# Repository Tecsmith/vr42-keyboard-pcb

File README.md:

# VR42 Keyboard PCB

<blockquote align="center"><b>NB:</b> This project design is complete, but has not been prototyped for validation.</blockquote>

## Intent

A 42-key micro keyboard designed for QMK with specific focus on ultra fast key scan rates / poll rates to make for an ideal gaming keyboard.

#### Progression

- See [CHANGELOG.md](CHANGELOG.md)

## Case

This case is designed in conjunction with the [VR42 Keyboard Case](https://github.com/tecsmith/vr42-keyboard-case).  These two projects are mutually inclusive and built as one solution.

## Resources

### Schematic
 - PDF [here](docs/vr42-revB.pdf)

### MCU PCB
 - EAGLE BRD *(PCB)* [here](EAGLE/vr42/vr42-revB-kbd.brd)
 - EAGLE SCH *(Schematic)* [here](EAGLE/vr42/vr42-revB-kbd.sch)

### Key Switch PCB
 - EAGLE BRD *(PCB)* [here](EAGLE/vr42/vr42-revB-kbd.brd)
 - EAGLE SCH *(Schematic)* [here](EAGLE/vr42/vr42-revB-kbd.sch)

### Beta PCB renders

#### Top

#### Bottom *(Component side)*

#### Intra-Board Connectors

You will need 3x Molex Pico-EZMate cables

|                                                                 | Cable | Usage                                |
|:---------------------------------------------------------------:|:-----:|:-------------------------------------|
| </img> | 6 way | Keyboard Matrix SPI interface        |
| </img> | 4 way | USB connection to UBD                |
| </img> | 3 way | ARGB to drive status & per-key LED's |

### Layout ideation renders

#### Render

#### Layout

#### Matrix coordinates *(QMK & VIA)*

## Planned Features

- [ ] QMK / VIA build
- [ ] 1x `STM32F405` STM32 CPU *(ft. dual USB, one is FS, the other HS)*
- [ ] 1x `TS3USB221` USB 2.0 Multiplexer for USB port selection *(based on [akeypad](https://github.com/luantty2/akeypad) )*
- [ ] 1x `USB3300-EZK` Hi-Speed USB Host for OTG PHY pin interface
- [ ] ~~1x `W25Q64JW` 8K SPI Flash Module~~ *[Not needed, the MCU has 512K Flash]*
- [ ] 1x `M95640-DRE` 8K SPI EEPROM Module
- [ ] 6x `MC74HC589A` SPI Input Shift Registers
    - No QMK key matrix, using all direct pins for faster scan rates
    - Scan via individually grounded keys on shift registers
- [ ] 2x `IS31FL3746B` SPI LED Matrix Drivers
    - 43x RGB LED's
    - With power on/off `TPS22995H-Q1` load switchs, 1 per
- [ ] C4 *(or S1)* UDB USB-C by @ai03 - see [here](https://github.com/ai03-2725/Unified-Daughterboard)

## Possible BIG issues

- [x] ~~With very limited PCB space, 13x IC's may not fit :(~~ *[Resolved with separate key and MCU PCB's]*
- [ ] ~~Not sure QMK can handle High Speed USB~~ *[It can, just now need to do it :( )]*
- [ ] Not sure dual USB is switchable with the USB multiplexer *[Needs to be coded for and tested]*
    - FS USB required for Bootloader
    - HS USB required for >1KHz polling rates

&nbsp;<br>&nbsp;
---
Made with &#9829; by **Vino Rodrigues**

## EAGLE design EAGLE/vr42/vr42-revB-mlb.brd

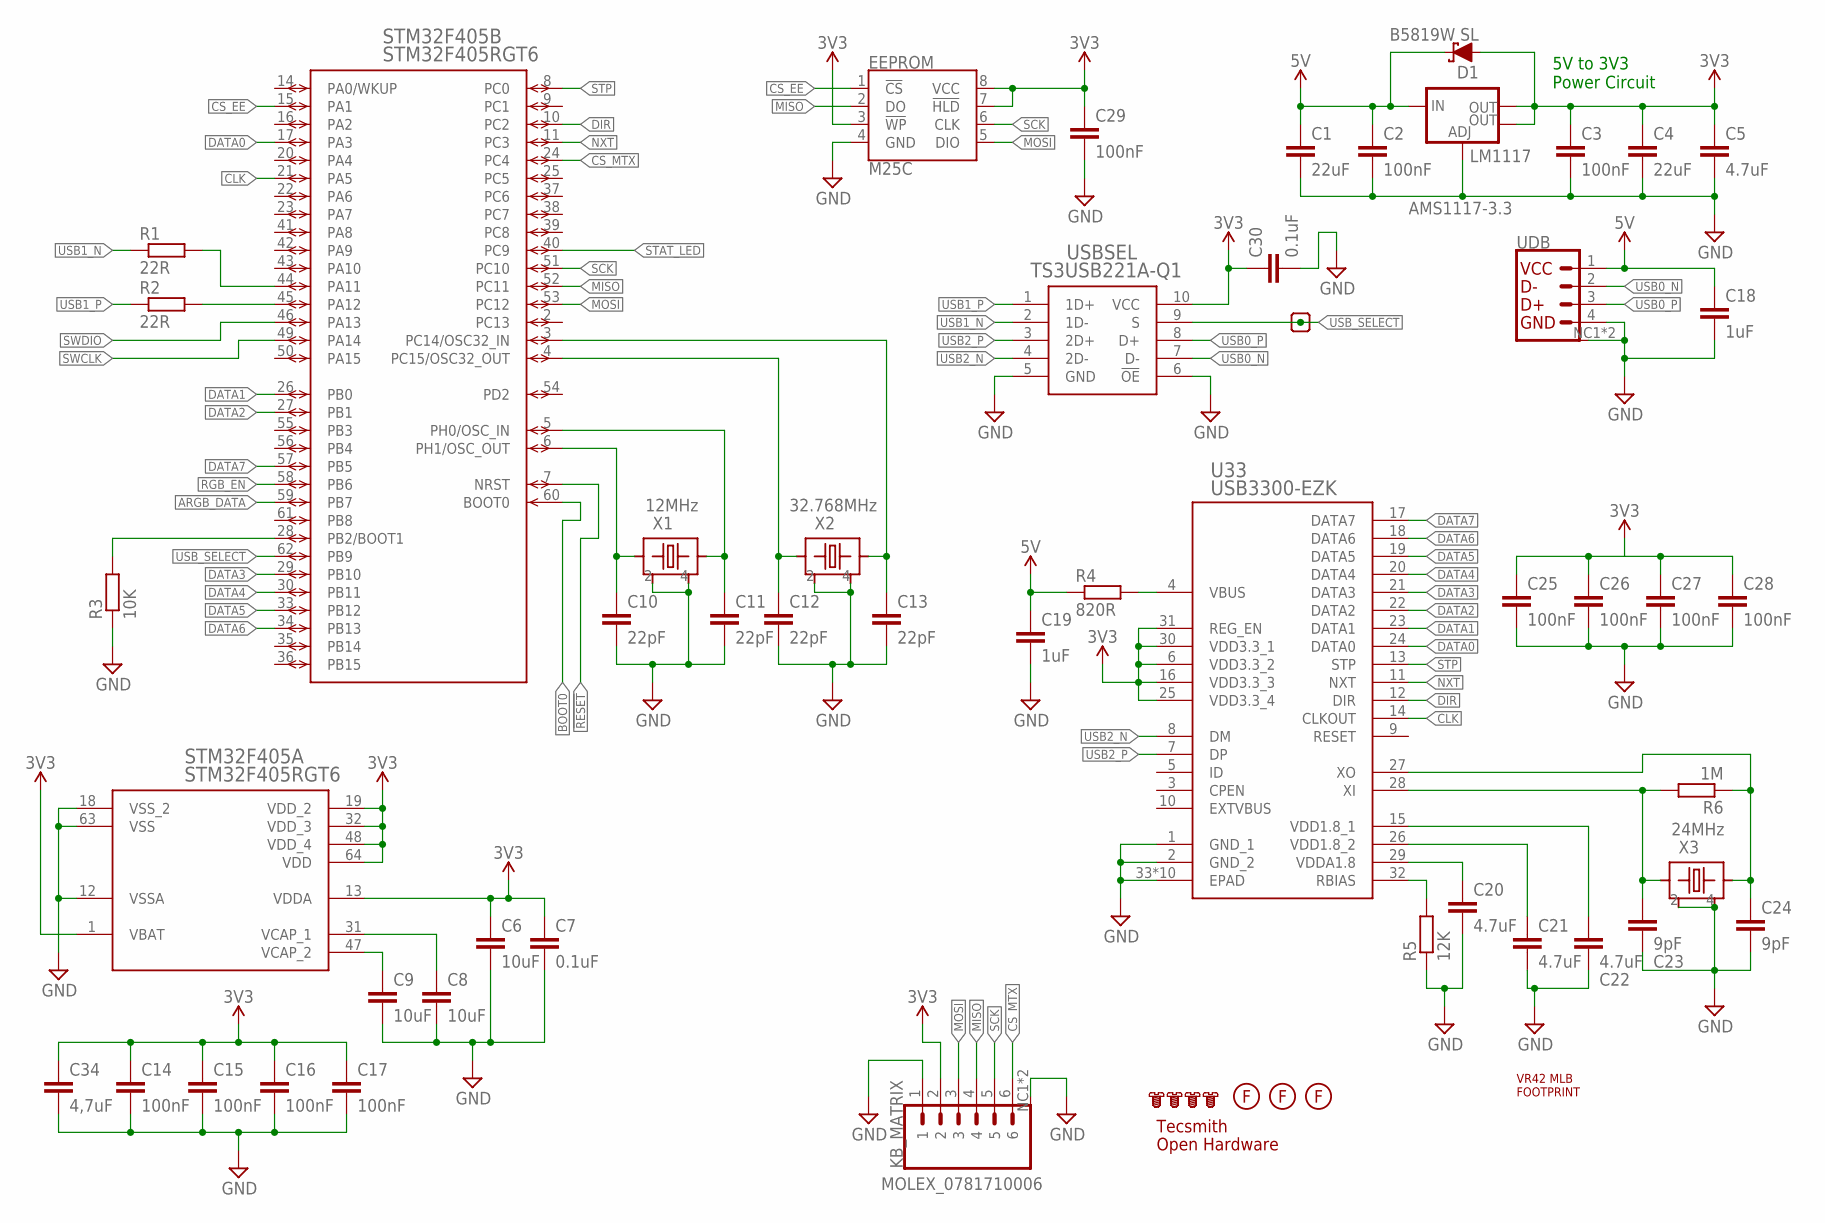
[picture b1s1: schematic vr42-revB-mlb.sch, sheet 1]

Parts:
C1, C4: 22uF; C0603
C2, C3, C14, C15, C16, C17, C25, C26, C27, C28, C29: 100nF; C0603
C5, C20, C21, C22: 4.7uF; C0603
C6, C8, C9: 10uF; C0603
C7, C30: 0.1uF; C0603
C10, C11, C12, C13: 22pF; C0603
C18, C19: 1uF; C0603
C23, C24: 9pF; C0603
C34: 4,7uF; C0603
D1: B5819W SL; SOD-123
EEPROM: M25C; 8-SOIC
KB_MATRIX: MOLEX_0781710006; MOLEX_781710006
LM1117: AMS1117-3.3; SOT223
LOGO1: OSHW-LOGOM; OSHW-LOGO-M
R1, R2: 22R; R0603
R3: 10K; R0603
R4: 820R; R0603
R5: 12K; R0603
R6: 1M; R0603
STM32F405: STM32F405RGT6; LQFP64-10X10MM
TP1: TEST-POINT.3RN; PAD.03X.03-RN
U33: USB3300-EZK; QFN32_5X5MC_MCH
U$1: VR42_MLB_FOOTPRINT
U$2, U$3, U$4, U$5: MOUNTING-HOLE
U$6: TECSMITH-LOGOLONG; TECSMITH-NAME
U$7, U$8, U$9: FIDUCIAL
UDB: UBD-S1_C4; MOLEX_781710004
USBSEL: TS3USB221A-Q1; RSE10
X1: 12MHz; CRYSTAL_2.5X2
X2: 32.768MHz; CRYSTAL_2.5X2
X3: 24MHz; CRYSTAL_2.5X2

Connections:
!RESET: STM32F405.7 (NRST); also elsewhere on the board
ARGB_DATA: STM32F405.59 (PB7); also elsewhere on the board
BOOT0: STM32F405.60 (BOOT0); also elsewhere on the board
BOOT1: R3.2, STM32F405.28 (PB2/BOOT1)
CLK: STM32F405.21 (PA5), U33.14 (CLKOUT)
CS_EE: EEPROM.1 (!CS), STM32F405.15 (PA1)
CS_MTX: KB_MATRIX.6, STM32F405.24 (PC4)
DATA0: STM32F405.17 (PA3), U33.24 (DATA0)
DATA1: STM32F405.26 (PB0), U33.23 (DATA1)
DATA2: STM32F405.27 (PB1), U33.22 (DATA2)
DATA3: STM32F405.29 (PB10), U33.21 (DATA3)
DATA4: STM32F405.30 (PB11), U33.20 (DATA4)
DATA5: STM32F405.33 (PB12), U33.19 (DATA5)
DATA6: STM32F405.34 (PB13), U33.18 (DATA6)
DATA7: STM32F405.57 (PB5), U33.17 (DATA7)
DIR: STM32F405.10 (PC2), U33.12 (DIR)
GND: C1.2, C2.2, C3.2, C4.2, C5.2, C6.2, C7.2, C8.2, C9.2, C10.2, C11.2, C12.2, C13.2, C14.2, C15.2, C16.2, C17.2, C18.2, C19.2, C20.2, C21.2, C22.2, C23.2, C24.2, C25.2, C26.2, C27.2, C28.2, C29.2, C30.2, C34.2, EEPROM.4 (GND), KB_MATRIX.1, KB_MATRIX.NC1 (M), KB_MATRIX.NC2 (M), LM1117.1 (ADJ), R3.1, R5.1, STM32F405.12 (VSSA), STM32F405.18 (VSS_2), STM32F405.63 (VSS), U33.1 (GND_1), U33.2 (GND_2), U33.33 (EPAD), U33.P$1 (EPAD), U33.P$2 (EPAD), U33.P$3 (EPAD), U33.P$4 (EPAD), U33.P$5 (EPAD), U33.P$6 (EPAD), U33.P$7 (EPAD), U33.P$8 (EPAD), U33.P$9 (EPAD), UDB.4 (GND), UDB.NC1 (M), UDB.NC2 (M), USBSEL.5 (GND), USBSEL.6 (!OE), X1.2, X1.4, X2.2, X2.4, X3.2, X3.4; also elsewhere on the board
MISO: EEPROM.2 (DO), KB_MATRIX.4, STM32F405.52 (PC11)
MOSI: EEPROM.5 (DIO), KB_MATRIX.3, STM32F405.53 (PC12)
unnamed: R1.2, STM32F405.44 (PA11)
unnamed: R2.2, STM32F405.45 (PA12)
unnamed: R4.2, U33.4 (VBUS)
unnamed: C20.1, U33.29 (VDDA1.8)
unnamed: C21.1, U33.26 (VDD1.8_2)
unnamed: C22.1, U33.15 (VDD1.8_1)
unnamed: C23.1, R6.2, U33.28 (XI), X3.1
unnamed: C24.1, R6.1, U33.27 (XO), X3.3
NXT: STM32F405.11 (PC3), U33.11 (NXT)
OSC32_IN: C13.1, STM32F405.3 (PC14/OSC32_IN), X2.3
OSC32_OUT: C12.1, STM32F405.4 (PC15/OSC32_OUT), X2.1
OSC_IN: C11.1, STM32F405.5 (PH0/OSC_IN), X1.3
OSC_OUT: C10.1, STM32F405.6 (PH1/OSC_OUT), X1.1
P$1: U$2.P$1, U$2.P$2, U$2.P$3, U$2.P$4, U$2.P$5, U$2.P$6, U$3.P$1, U$3.P$2, U$3.P$3, U$3.P$4, U$3.P$5, U$3.P$6, U$4.P$1, U$4.P$2, U$4.P$3, U$4.P$4, U$4.P$5, U$4.P$6, U$5.P$1, U$5.P$2, U$5.P$3, U$5.P$4, U$5.P$5, U$5.P$6
RBIAS: R5.2, U33.32 (RBIAS)
RGB_EN: STM32F405.58 (PB6); also elsewhere on the board
SCK: EEPROM.6 (CLK), KB_MATRIX.5, STM32F405.51 (PC10)
STAT_LED: STM32F405.40 (PC9); also elsewhere on the board
STP: STM32F405.8 (PC0), U33.13 (STP)
SWCLK: STM32F405.49 (PA14); also elsewhere on the board
SWDIO: STM32F405.46 (PA13); also elsewhere on the board
USB0_N: UDB.2 (DN), USBSEL.7 (D-)
USB0_P: UDB.3 (DP), USBSEL.8 (D+)
USB1_N: R1.1, USBSEL.2 (1D-)
USB1_P: R2.1, USBSEL.1 (1D+)
USB2_N: U33.8 (DM), USBSEL.4 (2D-)
USB2_P: U33.7 (DP), USBSEL.3 (2D+)
USB_SELECT: STM32F405.62 (PB9), TP1.1, USBSEL.9 (S)
VCAP1: C8.1, STM32F405.31 (VCAP_1)
VCAP2: C9.1, STM32F405.47 (VCAP_2)
VCC_1: C1.1, C2.1, C18.1, C19.1, D1.C, LM1117.3 (IN), R4.1, UDB.1 (VCC); also elsewhere on the board
VCC_2: C3.1, C4.1, C5.1, C6.1, C7.1, C14.1, C15.1, C16.1, C17.1, C25.1, C26.1, C27.1, C28.1, C29.1, C30.1, C34.1, D1.A, EEPROM.3 (!WP), EEPROM.7 (!HLD), EEPROM.8 (VCC), KB_MATRIX.2, LM1117.2 (OUT), LM1117.4 (OUT), STM32F405.1 (VBAT), STM32F405.13 (VDDA), STM32F405.19 (VDD_2), STM32F405.32 (VDD_3), STM32F405.48 (VDD_4), STM32F405.64 (VDD), U33.6 (VDD3.3_2), U33.16 (VDD3.3_3), U33.25 (VDD3.3_4), U33.30 (VDD3.3_1), U33.31 (REG_EN), USBSEL.10 (VCC); also elsewhere on the board

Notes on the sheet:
5V to 3V3 Power Circuit

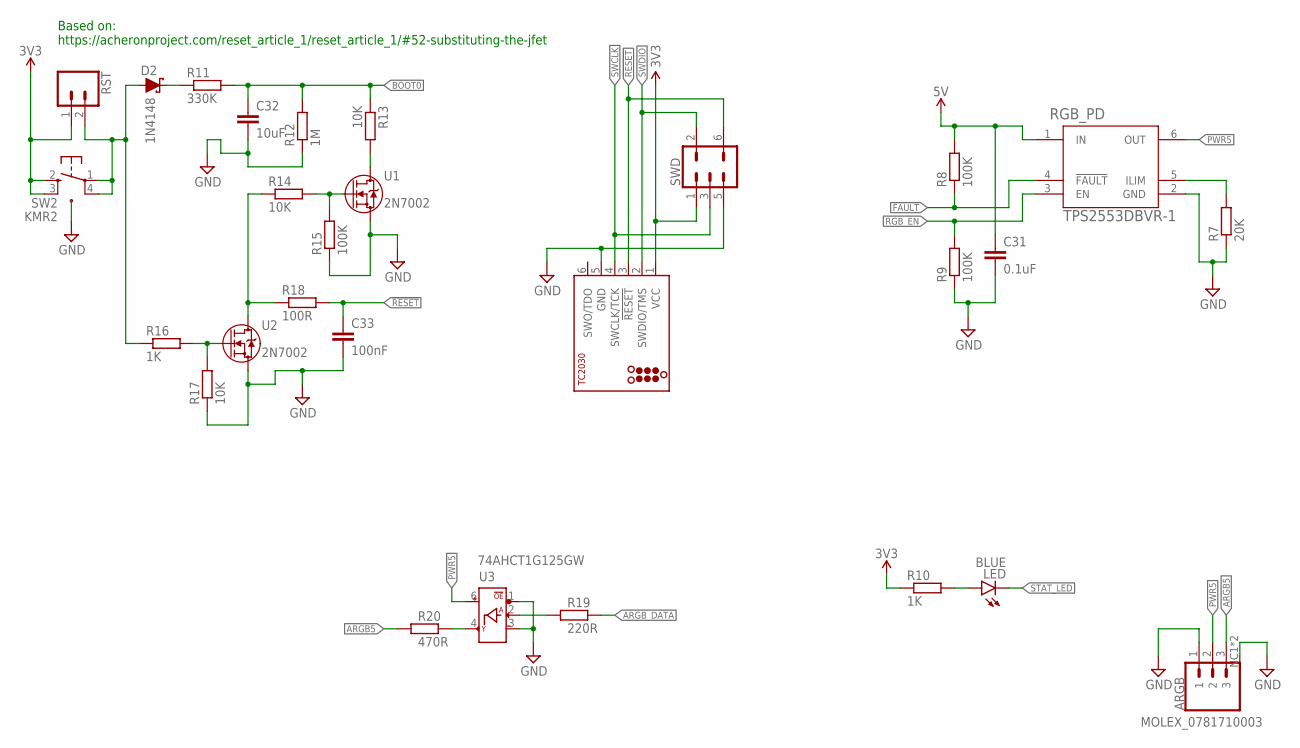
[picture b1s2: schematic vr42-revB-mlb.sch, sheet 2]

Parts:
ARGB: MOLEX_0781710003; MOLEX_781710003
C31: 0.1uF; C0603
C32: 10uF; C0603
C33: 100nF; C0603
D2: 1N4148; SOD-123
LED: BLUE; SML0603
R7: 20K; R0603
R8, R9, R15: 100K; R0603
R10, R16: 1K; R0603
R11: 330K; R0603
R12: 1M; R0603
R13, R14, R17: 10K; R0603
R18: 100R; R0603
R19: 220R; R0603
R20: 470R; R0603
RGB_PD: TPS2553DBVR-1; DBV0006A_N
RST: CONN_02; 1X02
SW2: KMR2; SW4_KMR221GLFS_CNK
SWD: SWD-5PIN; PAD_05_03X2_TP_NO4
TC: TC2030-MCP-NL
U1, U2: 2N7002; TO-236AB_NEX
U3: 74AHCT1G125GW; SC-88A__TSSOP5__SOT353-1

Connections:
!FAULT: R8.1, RGB_PD.4 (!FAULT)
!RESET: C33.1, R18.2, SWD.6, TC.3 (!RESET); also elsewhere on the board
ARGB5: ARGB.3, R20.1
ARGB_DATA: R19.2; also elsewhere on the board
BOOT0: C32.1, R11.2, R12.2, R13.1; also elsewhere on the board
GND: ARGB.1, ARGB.NC1 (M), ARGB.NC2 (M), C31.2, C32.2, C33.2, R7.1, R9.1, R12.1, R15.1, R17.1, RGB_PD.2 (GND), SW2.5, SWD.5, TC.5 (GND), U1.2 (3), U2.2 (3), U3.1 (!OE), U3.3 (3_GND); also elsewhere on the board
unnamed: D2.C, R11.1
unnamed: LED.A, R10.2
unnamed: R7.2, RGB_PD.5 (ILIM)
unnamed: R14.1, R18.1, U2.3 (2)
unnamed: R13.2, U1.3 (2)
unnamed: R14.2, R15.2, U1.1
unnamed: R19.1, U3.2 (A_DIN)
unnamed: R16.2, R17.2, U2.1
unnamed: D2.A, R16.1, RST.2, SW2.1, SW2.4
unnamed: R20.2, U3.4 (Y_DOUT)
PWR5: ARGB.2, RGB_PD.6 (OUT), U3.6 (5_VCC)
RGB_EN: R9.2, RGB_PD.3 (EN); also elsewhere on the board
STAT_LED: LED.C; also elsewhere on the board
SWCLK: SWD.3, TC.4 (SWCLK/TCK); also elsewhere on the board
SWDIO: SWD.2, TC.2 (SWDIO/TMS); also elsewhere on the board
VCC_1: C31.1, R8.2, RGB_PD.1 (IN); also elsewhere on the board
VCC_2: R10.1, RST.1, SW2.2, SW2.3, SWD.1, TC.1 (VCC); also elsewhere on the board

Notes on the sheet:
Based on: https://acheronproject.com/reset_article_1/reset_article_1/#52-substituting-the-jfet

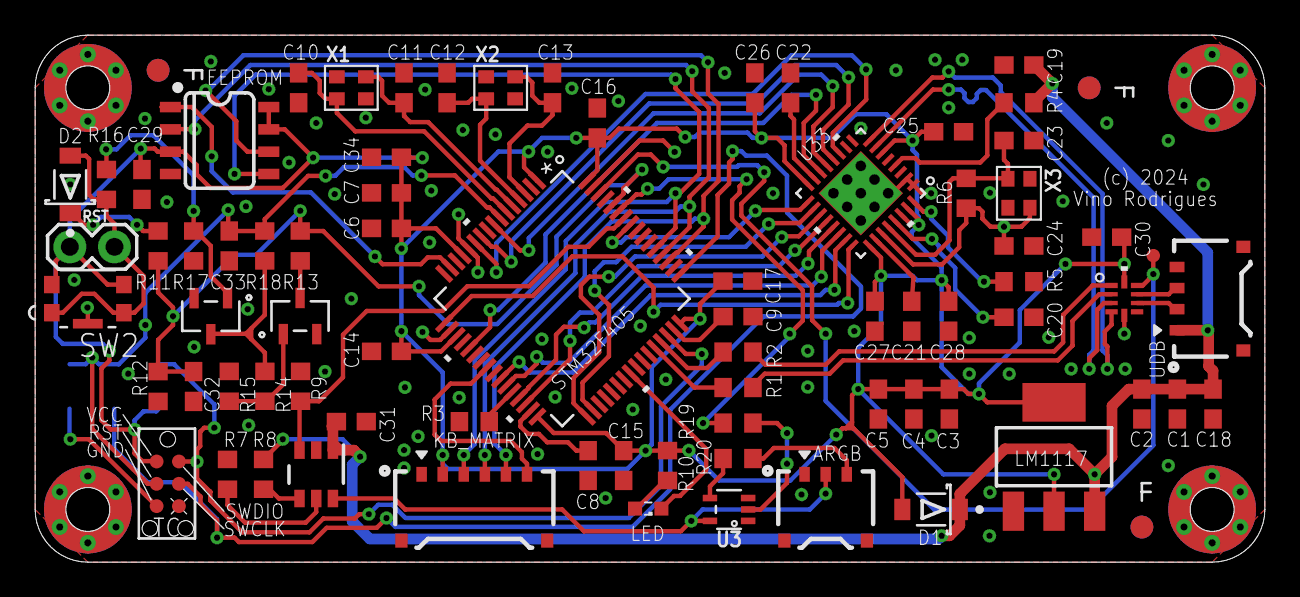
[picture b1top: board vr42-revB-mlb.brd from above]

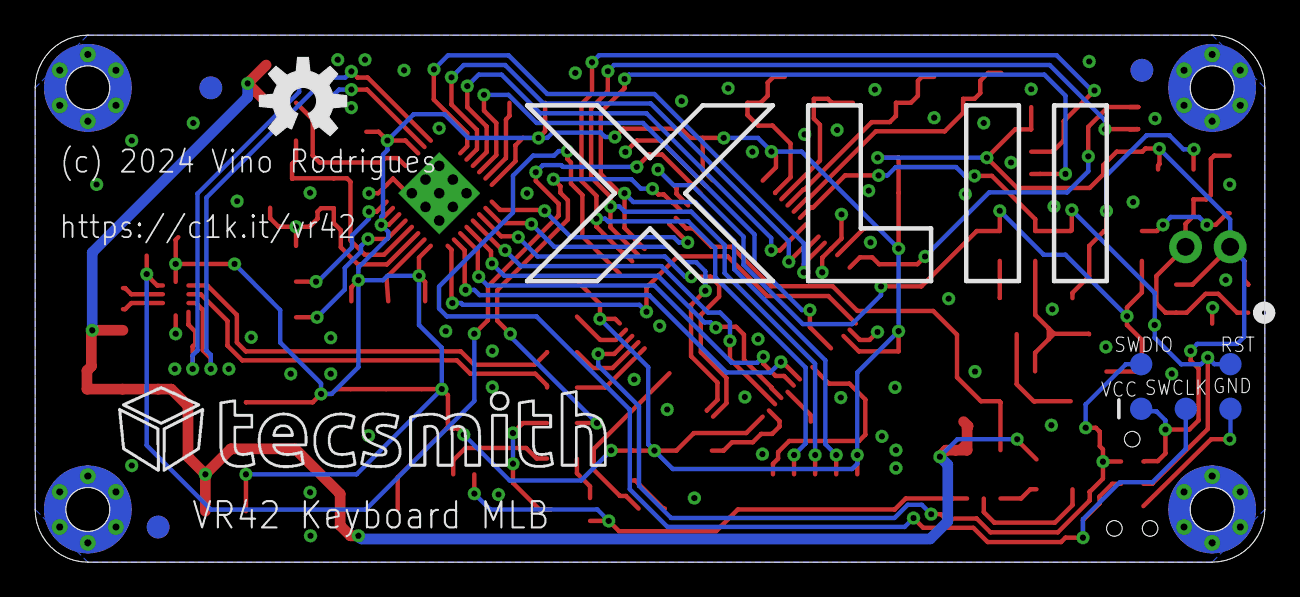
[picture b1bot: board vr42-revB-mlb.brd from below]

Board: 4 copper layers, 70.0 x 30.0 mm, 87 parts (3 on the bottom side), 64 nets.

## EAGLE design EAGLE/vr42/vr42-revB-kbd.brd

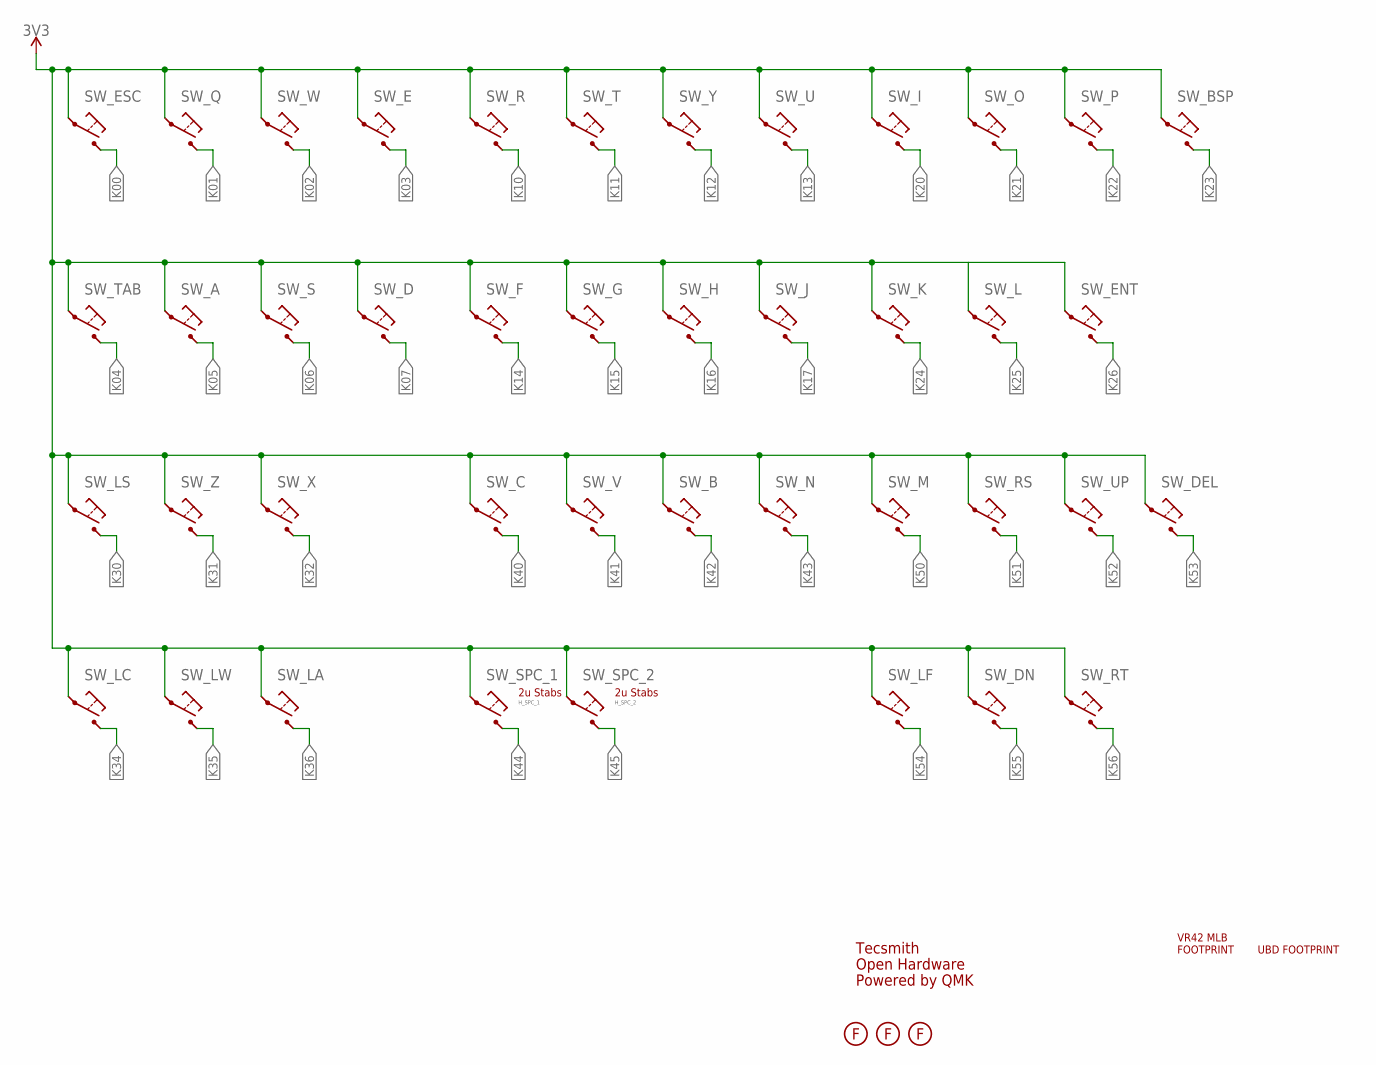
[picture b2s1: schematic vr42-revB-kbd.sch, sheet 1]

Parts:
H_SPC_1, H_SPC_2: MX-STABS-200U
LOGO1: OSHW-LOGOL; OSHW-LOGO-L
SW_A: MX-5-PIN-HOTSWAP-PAD
SW_B: MX-5-PIN-HOTSWAP-PAD
SW_BSP: MX-5-PIN-HOTSWAP-PAD
SW_C: MX-5-PIN-HOTSWAP-PAD
SW_D: MX-5-PIN-HOTSWAP-PAD
SW_DEL: MX-5-PIN-HOTSWAP-PAD
SW_DN: MX-5-PIN-HOTSWAP-PAD
SW_E: MX-5-PIN-HOTSWAP-PAD
SW_ENT: MX-5-PIN-HOTSWAP-PAD
SW_ESC: MX-5-PIN-HOTSWAP-PAD
SW_F: MX-5-PIN-HOTSWAP-PAD
SW_G: MX-5-PIN-HOTSWAP-PAD
SW_H: MX-5-PIN-HOTSWAP-PAD
SW_I: MX-5-PIN-HOTSWAP-PAD
SW_J: MX-5-PIN-HOTSWAP-PAD
SW_K: MX-5-PIN-HOTSWAP-PAD
SW_L: MX-5-PIN-HOTSWAP-PAD
SW_LA: MX-5-PIN-HOTSWAP-PAD
SW_LC: MX-5-PIN-HOTSWAP-PAD
SW_LF: MX-5-PIN-HOTSWAP-PAD
SW_LS: MX-5-PIN-HOTSWAP-PAD
SW_LW: MX-5-PIN-HOTSWAP-PAD
SW_M: MX-5-PIN-HOTSWAP-PAD
SW_N: MX-5-PIN-HOTSWAP-PAD
SW_O: MX-5-PIN-HOTSWAP-PAD
SW_P: MX-5-PIN-HOTSWAP-PAD
SW_Q: MX-5-PIN-HOTSWAP-PAD
SW_R: MX-5-PIN-HOTSWAP-PAD
SW_RS: MX-5-PIN-HOTSWAP-PAD
SW_RT: MX-5-PIN-HOTSWAP-PAD
SW_S: MX-5-PIN-HOTSWAP-PAD
SW_SPC_1, SW_SPC_2: MX-5-PIN-HOTSWAP-PAD
SW_T: MX-5-PIN-HOTSWAP-PAD
SW_TAB: MX-5-PIN-HOTSWAP-PAD
SW_U: MX-5-PIN-HOTSWAP-PAD
SW_UP: MX-5-PIN-HOTSWAP-PAD
SW_V: MX-5-PIN-HOTSWAP-PAD
SW_W: MX-5-PIN-HOTSWAP-PAD
SW_X: MX-5-PIN-HOTSWAP-PAD
SW_Y: MX-5-PIN-HOTSWAP-PAD
SW_Z: MX-5-PIN-HOTSWAP-PAD
U$1: VR42_MLB_FOOTPRINT
U$2: UBD_FOOTPRINT; UDB_FOOTPRINT
U$3: TECSMITH-LOGOLONG; TECSMITH-NAME
U$4: QMK_LOGO
U$5, U$6, U$7: FIDUCIAL

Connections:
K00: SW_ESC.1@1, SW_ESC.1@2; also elsewhere on the board
K01: SW_Q.1@1, SW_Q.1@2; also elsewhere on the board
K02: SW_W.1@1, SW_W.1@2; also elsewhere on the board
K03: SW_E.1@1, SW_E.1@2; also elsewhere on the board
K04: SW_TAB.1@1, SW_TAB.1@2; also elsewhere on the board
K05: SW_A.1@1, SW_A.1@2; also elsewhere on the board
K06: SW_S.1@1, SW_S.1@2; also elsewhere on the board
K07: SW_D.1@1, SW_D.1@2; also elsewhere on the board
K10: SW_R.1@1, SW_R.1@2; also elsewhere on the board
K11: SW_T.1@1, SW_T.1@2; also elsewhere on the board
K12: SW_Y.1@1, SW_Y.1@2; also elsewhere on the board
K13: SW_U.1@1, SW_U.1@2; also elsewhere on the board
K14: SW_F.1@1, SW_F.1@2; also elsewhere on the board
K15: SW_G.1@1, SW_G.1@2; also elsewhere on the board
K16: SW_H.1@1, SW_H.1@2; also elsewhere on the board
K17: SW_J.1@1, SW_J.1@2; also elsewhere on the board
K20: SW_I.1@1, SW_I.1@2; also elsewhere on the board
K21: SW_O.1@1, SW_O.1@2; also elsewhere on the board
K22: SW_P.1@1, SW_P.1@2; also elsewhere on the board
K23: SW_BSP.1@1, SW_BSP.1@2; also elsewhere on the board
K24: SW_K.1@1, SW_K.1@2; also elsewhere on the board
K25: SW_L.1@1, SW_L.1@2; also elsewhere on the board
K26: SW_ENT.1@1, SW_ENT.1@2; also elsewhere on the board
K30: SW_LS.1@1, SW_LS.1@2; also elsewhere on the board
K31: SW_Z.1@1, SW_Z.1@2; also elsewhere on the board
K32: SW_X.1@1, SW_X.1@2; also elsewhere on the board
K34: SW_LC.1@1, SW_LC.1@2; also elsewhere on the board
K35: SW_LW.1@1, SW_LW.1@2; also elsewhere on the board
K36: SW_LA.1@1, SW_LA.1@2; also elsewhere on the board
K40: SW_C.1@1, SW_C.1@2; also elsewhere on the board
K41: SW_V.1@1, SW_V.1@2; also elsewhere on the board
K42: SW_B.1@1, SW_B.1@2; also elsewhere on the board
K43: SW_N.1@1, SW_N.1@2; also elsewhere on the board
K44: SW_SPC_1.1@1, SW_SPC_1.1@2; also elsewhere on the board
K45: SW_SPC_2.1@1, SW_SPC_2.1@2; also elsewhere on the board
K50: SW_M.1@1, SW_M.1@2; also elsewhere on the board
K51: SW_RS.1@1, SW_RS.1@2; also elsewhere on the board
K52: SW_UP.1@1, SW_UP.1@2; also elsewhere on the board
K53: SW_DEL.1@1, SW_DEL.1@2; also elsewhere on the board
K54: SW_LF.1@1, SW_LF.1@2; also elsewhere on the board
K55: SW_DN.1@1, SW_DN.1@2; also elsewhere on the board
K56: SW_RT.1@1, SW_RT.1@2; also elsewhere on the board
VCC_2: SW_A.2@1 (S), SW_A.2@2 (S), SW_B.2@1 (S), SW_B.2@2 (S), SW_BSP.2@1 (S), SW_BSP.2@2 (S), SW_C.2@1 (S), SW_C.2@2 (S), SW_D.2@1 (S), SW_D.2@2 (S), SW_DEL.2@1 (S), SW_DEL.2@2 (S), SW_DN.2@1 (S), SW_DN.2@2 (S), SW_E.2@1 (S), SW_E.2@2 (S), SW_ENT.2@1 (S), SW_ENT.2@2 (S), SW_ESC.2@1 (S), SW_ESC.2@2 (S), SW_F.2@1 (S), SW_F.2@2 (S), SW_G.2@1 (S), SW_G.2@2 (S), SW_H.2@1 (S), SW_H.2@2 (S), SW_I.2@1 (S), SW_I.2@2 (S), SW_J.2@1 (S), SW_J.2@2 (S), SW_K.2@1 (S), SW_K.2@2 (S), SW_L.2@1 (S), SW_L.2@2 (S), SW_LA.2@1 (S), SW_LA.2@2 (S), SW_LC.2@1 (S), SW_LC.2@2 (S), SW_LF.2@1 (S), SW_LF.2@2 (S), SW_LS.2@1 (S), SW_LS.2@2 (S), SW_LW.2@1 (S), SW_LW.2@2 (S), SW_M.2@1 (S), SW_M.2@2 (S), SW_N.2@1 (S), SW_N.2@2 (S), SW_O.2@1 (S), SW_O.2@2 (S), SW_P.2@1 (S), SW_P.2@2 (S), SW_Q.2@1 (S), SW_Q.2@2 (S), SW_R.2@1 (S), SW_R.2@2 (S), SW_RS.2@1 (S), SW_RS.2@2 (S), SW_RT.2@1 (S), SW_RT.2@2 (S), SW_S.2@1 (S), SW_S.2@2 (S), SW_SPC_1.2@1 (S), SW_SPC_1.2@2 (S), SW_SPC_2.2@1 (S), SW_SPC_2.2@2 (S), SW_T.2@1 (S), SW_T.2@2 (S), SW_TAB.2@1 (S), SW_TAB.2@2 (S), SW_U.2@1 (S), SW_U.2@2 (S), SW_UP.2@1 (S), SW_UP.2@2 (S), SW_V.2@1 (S), SW_V.2@2 (S), SW_W.2@1 (S), SW_W.2@2 (S), SW_X.2@1 (S), SW_X.2@2 (S), SW_Y.2@1 (S), SW_Y.2@2 (S), SW_Z.2@1 (S), SW_Z.2@2 (S); also elsewhere on the board

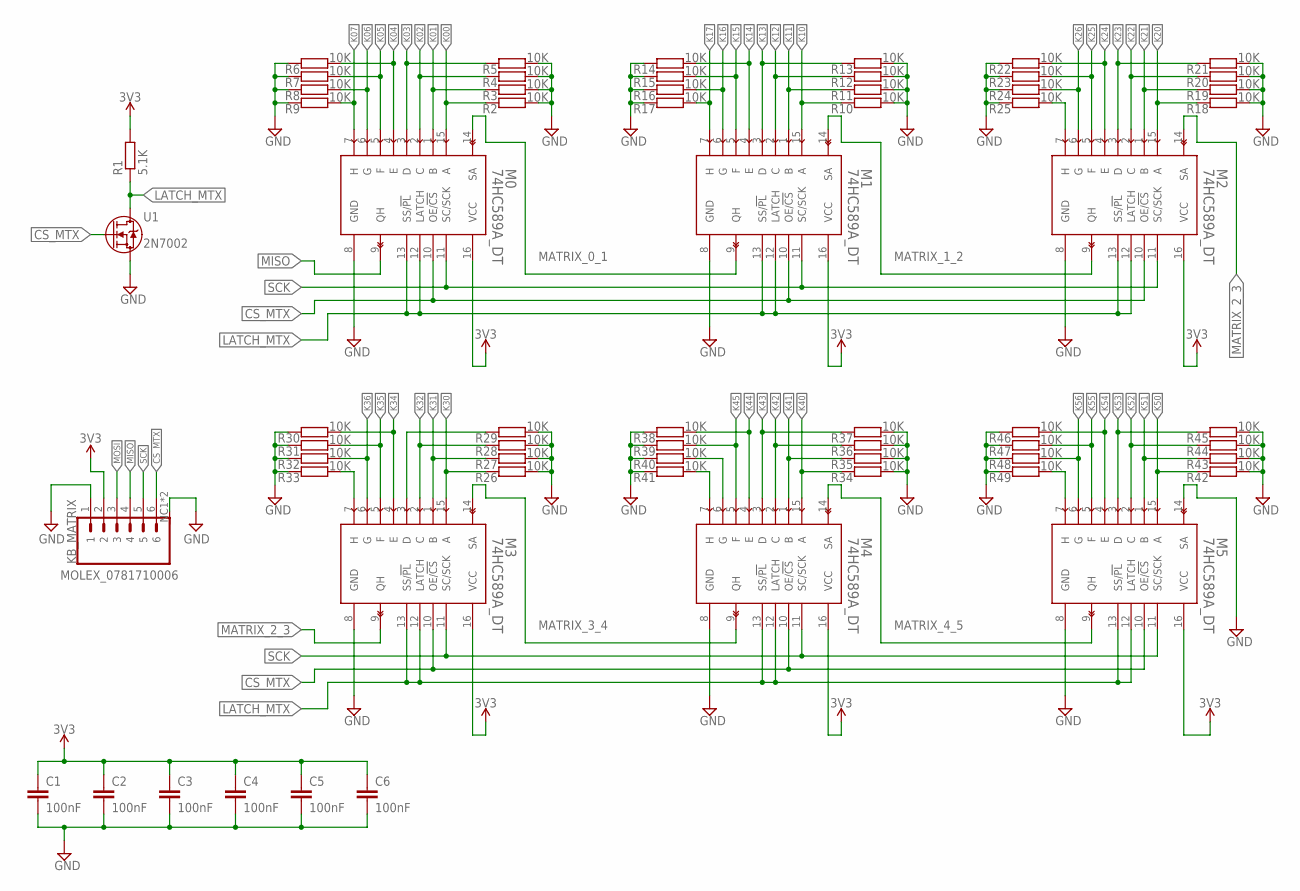
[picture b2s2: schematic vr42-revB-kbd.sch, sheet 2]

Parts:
C1, C2, C3, C4, C5, C6: 100nF; C0603
KB_MATRIX: MOLEX_0781710006; MOLEX_781710006
M0, M1, M2, M3, M4, M5: 74HC589A_DT; TSSOP16
R1: 5.1K; R0603
R2, R3, R4, R5, R6, R7, R8, R9, R10, R11, R12, R13, R14, R15, R16, R17, R18, R19, R20, R21, R22, R23, R24, R25, R26, R27, R28, R29, R30, R31, R32, R33, R34, R35, R36, R37, R38, R39, R40, R41, R42, R43, R44, R45, R46, R47, R48, R49: 10K; R0603
U1: 2N7002; TO-236AB_NEX

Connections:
CS_MTX: KB_MATRIX.6, M0.10 (OE/!CS), M1.10 (OE/!CS), M2.10 (OE/!CS), M3.10 (OE/!CS), M4.10 (OE/!CS), M5.10 (OE/!CS), U1.1
GND: C1.2, C2.2, C3.2, C4.2, C5.2, C6.2, KB_MATRIX.1, KB_MATRIX.NC1 (M), KB_MATRIX.NC2 (M), M0.8 (GND), M1.8 (GND), M2.8 (GND), M3.8 (GND), M4.8 (GND), M5.8 (GND), M5.14 (SA), R2.1, R3.1, R4.1, R5.1, R6.2, R7.2, R8.2, R9.2, R10.1, R11.1, R12.1, R13.1, R14.2, R15.2, R16.2, R17.2, R18.1, R19.1, R20.1, R21.1, R22.2, R23.2, R24.2, R25.2, R26.1, R27.1, R28.1, R29.1, R30.2, R31.2, R32.2, R33.2, R34.1, R35.1, R36.1, R37.1, R38.2, R39.2, R40.2, R41.2, R42.1, R43.1, R44.1, R45.1, R46.2, R47.2, R48.2, R49.2, U1.2 (3); also elsewhere on the board
K00: M0.15 (A), R2.2; also elsewhere on the board
K01: M0.1 (B), R3.2; also elsewhere on the board
K02: M0.2 (C), R4.2; also elsewhere on the board
K03: M0.3 (D), R5.2; also elsewhere on the board
K04: M0.4 (E), R6.1; also elsewhere on the board
K05: M0.5 (F), R7.1; also elsewhere on the board
K06: M0.6 (G), R8.1; also elsewhere on the board
K07: M0.7 (H), R9.1; also elsewhere on the board
K10: M1.15 (A), R10.2; also elsewhere on the board
K11: M1.1 (B), R11.2; also elsewhere on the board
K12: M1.2 (C), R12.2; also elsewhere on the board
K13: M1.3 (D), R13.2; also elsewhere on the board
K14: M1.4 (E), R14.1; also elsewhere on the board
K15: M1.5 (F), R15.1; also elsewhere on the board
K16: M1.6 (G), R16.1; also elsewhere on the board
K17: M1.7 (H), R17.1; also elsewhere on the board
K20: M2.15 (A), R18.2; also elsewhere on the board
K21: M2.1 (B), R19.2; also elsewhere on the board
K22: M2.2 (C), R20.2; also elsewhere on the board
K23: M2.3 (D), R21.2; also elsewhere on the board
K24: M2.4 (E), R22.1; also elsewhere on the board
K25: M2.5 (F), R23.1; also elsewhere on the board
K26: M2.6 (G), R24.1; also elsewhere on the board
K27: M2.7 (H), R25.1
K30: M3.15 (A), R26.2; also elsewhere on the board
K31: M3.1 (B), R27.2; also elsewhere on the board
K32: M3.2 (C), R28.2; also elsewhere on the board
K33: M3.3 (D), R29.2
K34: M3.4 (E), R30.1; also elsewhere on the board
K35: M3.5 (F), R31.1; also elsewhere on the board
K36: M3.6 (G), R32.1; also elsewhere on the board
K37: M3.7 (H), R33.1
K40: M4.15 (A), R34.2; also elsewhere on the board
K41: M4.1 (B), R35.2; also elsewhere on the board
K42: M4.2 (C), R36.2; also elsewhere on the board
K43: M4.3 (D), R37.2; also elsewhere on the board
K44: M4.4 (E), R38.1; also elsewhere on the board
K45: M4.5 (F), R39.1; also elsewhere on the board
K46: M4.6 (G), R40.1
K47: M4.7 (H), R41.1
K50: M5.15 (A), R42.2; also elsewhere on the board
K51: M5.1 (B), R43.2; also elsewhere on the board
K52: M5.2 (C), R44.2; also elsewhere on the board
K53: M5.3 (D), R45.2; also elsewhere on the board
K54: M5.4 (E), R46.1; also elsewhere on the board
K55: M5.5 (F), R47.1; also elsewhere on the board
K56: M5.6 (G), R48.1; also elsewhere on the board
K57: M5.7 (H), R49.1
LATCH_MTX: M0.12 (LATCH), M0.13 (SS/!PL), M1.12 (LATCH), M1.13 (SS/!PL), M2.12 (LATCH), M2.13 (SS/!PL), M3.12 (LATCH), M3.13 (SS/!PL), M4.12 (LATCH), M4.13 (SS/!PL), M5.12 (LATCH), M5.13 (SS/!PL), R1.1, U1.3 (2)
MATRIX_0_1: M0.14 (SA), M1.9 (QH)
MATRIX_1_2: M1.14 (SA), M2.9 (QH)
MATRIX_2_3: M2.14 (SA), M3.9 (QH)
MATRIX_3_4: M3.14 (SA), M4.9 (QH)
MATRIX_4_5: M4.14 (SA), M5.9 (QH)
MISO: KB_MATRIX.4, M0.9 (QH)
MOSI: KB_MATRIX.3
SCK: KB_MATRIX.5, M0.11 (SC/SCK), M1.11 (SC/SCK), M2.11 (SC/SCK), M3.11 (SC/SCK), M4.11 (SC/SCK), M5.11 (SC/SCK)
VCC_2: C1.1, C2.1, C3.1, C4.1, C5.1, C6.1, KB_MATRIX.2, M0.16 (VCC), M1.16 (VCC), M2.16 (VCC), M3.16 (VCC), M4.16 (VCC), M5.16 (VCC), R1.2; also elsewhere on the board

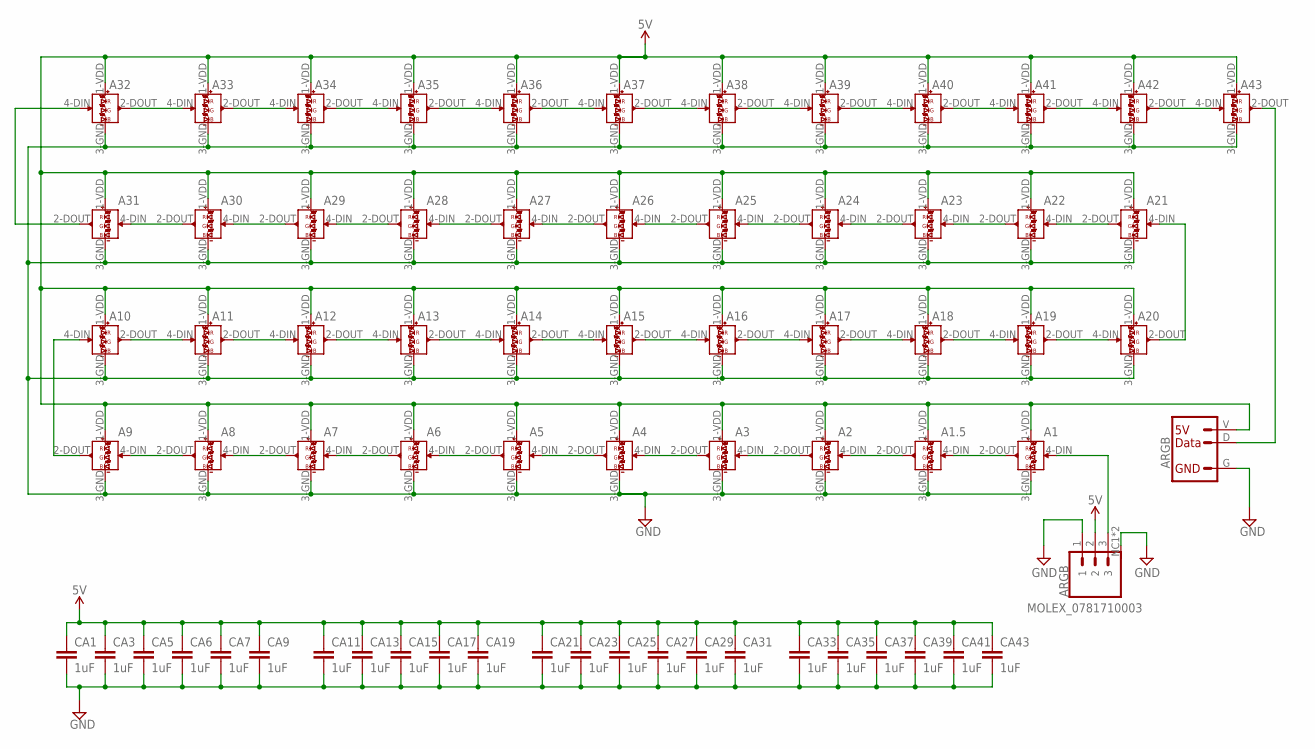
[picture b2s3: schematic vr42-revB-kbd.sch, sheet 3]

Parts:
A1, A1.5, A2, A3, A4, A5, A6, A7, A8, A9, A10, A11, A12, A13, A14, A15, A16, A17, A18, A19, A20, A21, A22, A23, A24, A25, A26, A27, A28, A29, A30, A31, A32, A33, A34, A35, A36, A37, A38, A39, A40, A41, A42, A43: SK6812-E-REVERSE_V2; SK6812-E-MILL_V2
ARGB: MOLEX_0781710003; MOLEX_781710003
CA1, CA3, CA5, CA6, CA7, CA9, CA11, CA13, CA15, CA17, CA19, CA21, CA23, CA25, CA27, CA29, CA31, CA33, CA35, CA37, CA39, CA41, CA43: 1uF; C0603
I44: ARGB

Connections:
GND: A1.3-GND (3_GND), A1.5.3-GND (3_GND), A2.3-GND (3_GND), A3.3-GND (3_GND), A4.3-GND (3_GND), A5.3-GND (3_GND), A6.3-GND (3_GND), A7.3-GND (3_GND), A8.3-GND (3_GND), A9.3-GND (3_GND), A10.3-GND (3_GND), A11.3-GND (3_GND), A12.3-GND (3_GND), A13.3-GND (3_GND), A14.3-GND (3_GND), A15.3-GND (3_GND), A16.3-GND (3_GND), A17.3-GND (3_GND), A18.3-GND (3_GND), A19.3-GND (3_GND), A20.3-GND (3_GND), A21.3-GND (3_GND), A22.3-GND (3_GND), A23.3-GND (3_GND), A24.3-GND (3_GND), A25.3-GND (3_GND), A26.3-GND (3_GND), A27.3-GND (3_GND), A28.3-GND (3_GND), A29.3-GND (3_GND), A30.3-GND (3_GND), A31.3-GND (3_GND), A32.3-GND (3_GND), A33.3-GND (3_GND), A34.3-GND (3_GND), A35.3-GND (3_GND), A36.3-GND (3_GND), A37.3-GND (3_GND), A38.3-GND (3_GND), A39.3-GND (3_GND), A40.3-GND (3_GND), A41.3-GND (3_GND), A42.3-GND (3_GND), A43.3-GND (3_GND), ARGB.1, ARGB.NC1 (M), ARGB.NC2 (M), CA1.2, CA3.2, CA5.2, CA6.2, CA7.2, CA9.2, CA11.2, CA13.2, CA15.2, CA17.2, CA19.2, CA21.2, CA23.2, CA25.2, CA27.2, CA29.2, CA31.2, CA33.2, CA35.2, CA37.2, CA39.2, CA41.2, CA43.2, I44.G; also elsewhere on the board
unnamed: A1.4-DIN (4_DIN), ARGB.3
unnamed: A43.2-DOUT (2_DOUT), I44.D
unnamed: A9.2-DOUT (2_DOUT), A10.4-DIN (4_DIN)
unnamed: A32.2-DOUT (2_DOUT), A33.4-DIN (4_DIN)
unnamed: A33.2-DOUT (2_DOUT), A34.4-DIN (4_DIN)
unnamed: A34.2-DOUT (2_DOUT), A35.4-DIN (4_DIN)
unnamed: A35.2-DOUT (2_DOUT), A36.4-DIN (4_DIN)
unnamed: A36.2-DOUT (2_DOUT), A37.4-DIN (4_DIN)
unnamed: A1.5.2-DOUT (2_DOUT), A2.4-DIN (4_DIN)
unnamed: A1.2-DOUT (2_DOUT), A1.5.4-DIN (4_DIN)
unnamed: A37.2-DOUT (2_DOUT), A38.4-DIN (4_DIN)
unnamed: A38.2-DOUT (2_DOUT), A39.4-DIN (4_DIN)
unnamed: A39.2-DOUT (2_DOUT), A40.4-DIN (4_DIN)
unnamed: A23.2-DOUT (2_DOUT), A24.4-DIN (4_DIN)
unnamed: A24.2-DOUT (2_DOUT), A25.4-DIN (4_DIN)
unnamed: A25.2-DOUT (2_DOUT), A26.4-DIN (4_DIN)
unnamed: A26.2-DOUT (2_DOUT), A27.4-DIN (4_DIN)
unnamed: A27.2-DOUT (2_DOUT), A28.4-DIN (4_DIN)
unnamed: A29.2-DOUT (2_DOUT), A30.4-DIN (4_DIN)
unnamed: A30.2-DOUT (2_DOUT), A31.4-DIN (4_DIN)
unnamed: A20.2-DOUT (2_DOUT), A21.4-DIN (4_DIN)
unnamed: A10.2-DOUT (2_DOUT), A11.4-DIN (4_DIN)
unnamed: A11.2-DOUT (2_DOUT), A12.4-DIN (4_DIN)
unnamed: A12.2-DOUT (2_DOUT), A13.4-DIN (4_DIN)
unnamed: A13.2-DOUT (2_DOUT), A14.4-DIN (4_DIN)
unnamed: A14.2-DOUT (2_DOUT), A15.4-DIN (4_DIN)
unnamed: A15.2-DOUT (2_DOUT), A16.4-DIN (4_DIN)
unnamed: A16.2-DOUT (2_DOUT), A17.4-DIN (4_DIN)
unnamed: A40.2-DOUT (2_DOUT), A41.4-DIN (4_DIN)
unnamed: A5.2-DOUT (2_DOUT), A6.4-DIN (4_DIN)
unnamed: A6.2-DOUT (2_DOUT), A7.4-DIN (4_DIN)
unnamed: A7.2-DOUT (2_DOUT), A8.4-DIN (4_DIN)
unnamed: A8.2-DOUT (2_DOUT), A9.4-DIN (4_DIN)
unnamed: A31.2-DOUT (2_DOUT), A32.4-DIN (4_DIN)
unnamed: A19.2-DOUT (2_DOUT), A20.4-DIN (4_DIN)
unnamed: A41.2-DOUT (2_DOUT), A42.4-DIN (4_DIN)
unnamed: A28.2-DOUT (2_DOUT), A29.4-DIN (4_DIN)
unnamed: A42.2-DOUT (2_DOUT), A43.4-DIN (4_DIN)
unnamed: A21.2-DOUT (2_DOUT), A22.4-DIN (4_DIN)
unnamed: A22.2-DOUT (2_DOUT), A23.4-DIN (4_DIN)
unnamed: A2.2-DOUT (2_DOUT), A3.4-DIN (4_DIN)
unnamed: A3.2-DOUT (2_DOUT), A4.4-DIN (4_DIN)
unnamed: A4.2-DOUT (2_DOUT), A5.4-DIN (4_DIN)
unnamed: A17.2-DOUT (2_DOUT), A18.4-DIN (4_DIN)
unnamed: A18.2-DOUT (2_DOUT), A19.4-DIN (4_DIN)
VCC_1: A1.1-VDD (1_VDD), A1.5.1-VDD (1_VDD), A2.1-VDD (1_VDD), A3.1-VDD (1_VDD), A4.1-VDD (1_VDD), A5.1-VDD (1_VDD), A6.1-VDD (1_VDD), A7.1-VDD (1_VDD), A8.1-VDD (1_VDD), A9.1-VDD (1_VDD), A10.1-VDD (1_VDD), A11.1-VDD (1_VDD), A12.1-VDD (1_VDD), A13.1-VDD (1_VDD), A14.1-VDD (1_VDD), A15.1-VDD (1_VDD), A16.1-VDD (1_VDD), A17.1-VDD (1_VDD), A18.1-VDD (1_VDD), A19.1-VDD (1_VDD), A20.1-VDD (1_VDD), A21.1-VDD (1_VDD), A22.1-VDD (1_VDD), A23.1-VDD (1_VDD), A24.1-VDD (1_VDD), A25.1-VDD (1_VDD), A26.1-VDD (1_VDD), A27.1-VDD (1_VDD), A28.1-VDD (1_VDD), A29.1-VDD (1_VDD), A30.1-VDD (1_VDD), A31.1-VDD (1_VDD), A32.1-VDD (1_VDD), A33.1-VDD (1_VDD), A34.1-VDD (1_VDD), A35.1-VDD (1_VDD), A36.1-VDD (1_VDD), A37.1-VDD (1_VDD), A38.1-VDD (1_VDD), A39.1-VDD (1_VDD), A40.1-VDD (1_VDD), A41.1-VDD (1_VDD), A42.1-VDD (1_VDD), A43.1-VDD (1_VDD), ARGB.2, CA1.1, CA3.1, CA5.1, CA6.1, CA7.1, CA9.1, CA11.1, CA13.1, CA15.1, CA17.1, CA19.1, CA21.1, CA23.1, CA25.1, CA27.1, CA29.1, CA31.1, CA33.1, CA35.1, CA37.1, CA39.1, CA41.1, CA43.1, I44.V

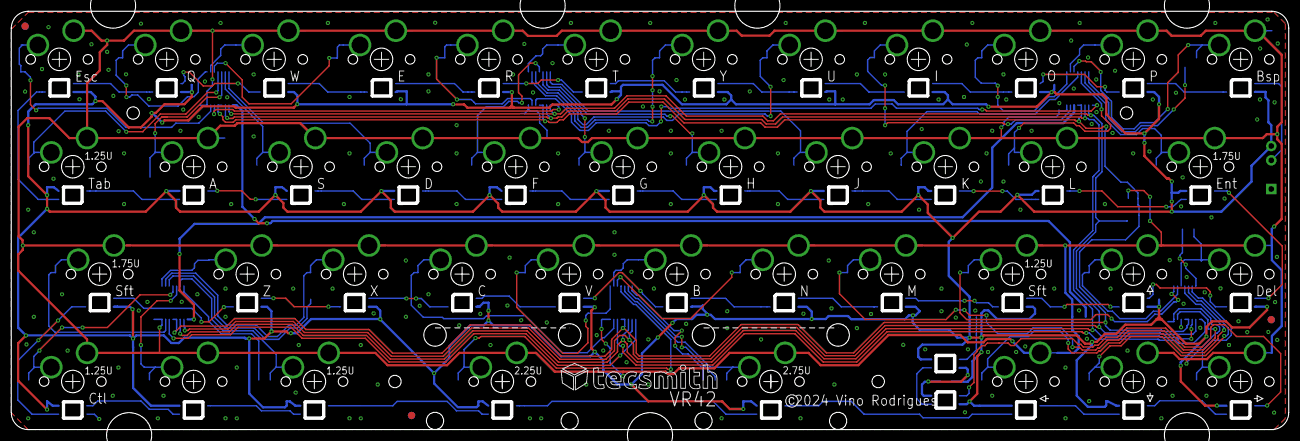
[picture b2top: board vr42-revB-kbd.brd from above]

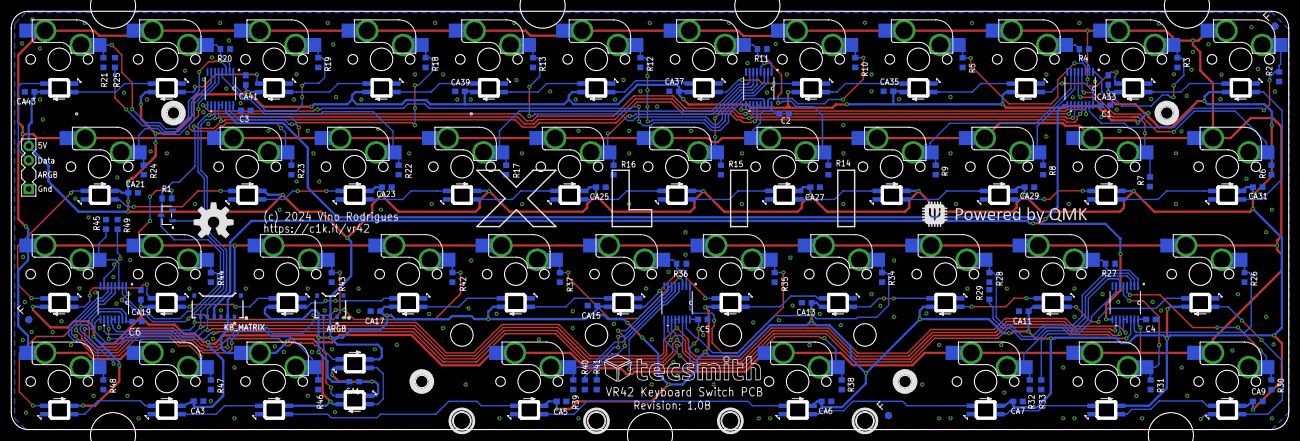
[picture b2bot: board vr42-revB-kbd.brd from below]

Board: 2 copper layers, 226.6 x 74.2 mm, 185 parts (91 on the bottom side), 105 nets.

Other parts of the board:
U$8: TECSMITH-LOGOLONG; TECSMITH-NAME

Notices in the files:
EAGLE/udb/usb-db-revC.brd:
(c) 2019
EAGLE/vr42/vr42-revB-kbd.brd:
(c) 2024 Vino Rodrigues
EAGLE/vr42/vr42-revB-mlb.brd:
(c) 2024
parts and their libraries:
SparkFun-Capacitors: Licensing: Creative Commons ShareAlike 4.0 International - https://creativecommons.org/licenses/by-sa/4.0
COPYRIGHT: Copyright (C) 2023 Ultra Librarian. All rights reserved.
COPYRIGHT: Copyright (C) 2024 Ultra Librarian. All rights reserved.
